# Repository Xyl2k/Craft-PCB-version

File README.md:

# CRAFT AVR Demo — Custom PCB and 3D Enclosure

This repository contains a custom **double-layer PCB** design and a **3D-printable enclosure** for running the [CRAFT demo](http://www.linusakesson.net/scene/craft/) by Linus Åkesson on an **ATmega88-20PU** microcontroller.

The project is developed in **Autodesk EAGLE** for the PCB layout and includes an **STL enclosure model** designed for FDM 3D printing.

---

## 📦 Contents

- `eagle/`: EAGLE schematic (`.sch`) and board layout (`.brd`)
- `enclosure/`: 3D enclosure model (`.stl`)
- `firmware/`: Precompiled HEX file and Flipper Zero-compatible firmware folder
- `README.md`: Project documentation

---

## ⚙️ Features

- Runs the original CRAFT demo at **20 MHz**
- Audio synthesized in real-time by the ATmega88
- Double-layer PCB with clear silkscreen labeling
- Compact size with mounting holes for enclosure
- Powered via ISP header or screw terminal in 3.3 volts

---

## 📋 Bill of Materials (BOM)

| Qty | Component              | Value/Type         |
|-----|------------------------|--------------------|
| x7  | Resistor               | 2 kΩ               |
| x6  | Resistor               | 1 kΩ               |
| x9  | Resistor               | 442 Ω              |
| x3  | Resistor               | 220 Ω              |
| x2  | Capacitor              | 22 pF              |
| x1  | Capacitor              | 10 µF              |
| x3  | Diode                  | 1N4148             |
| x1  | Transistor             | BC560C             |
| x1  | Trimmer Potentiometer  | 1 kΩ               |
| x1  | Microcontroller        | ATmega88-20PU      |
| x1  | Crystal Oscillator     | 20 MHz             |
| x1  | VGA Socket (Female)    | Through-hole       |
| x1  | RCA Socket (Female)    | Through-hole       |
| x1  | Screw Terminal         | 2-pin              |

---

## 🖨️ Enclosure

- Format: `.stl` for 3D printing
- Designed for FDM printers (0.4 mm nozzle recommended)
- Includes cutouts for VGA, RCA, power terminal, and ISP pins
- Snap-fit
- PCB enclosure case.STL need to be printed with support.

---

## 🛠️ Flashing the Firmware

The `firmware/` folder includes:

- `flash.hex` — Precompiled firmware for ATmega88-20PU
- `AVR Flasher/` — Folder structure compatible with **Flipper Zero**

### 🔧 Flashing with Flipper Zero

1. Copy the content of `AVR Flasher/` folder to your Flipper Zero's SD card in (`/apps_data/avr_isp/`).
2. Connect your Flipper to the CRAFT PCB via the ISP header.
3. Open the [**AVR Flasher**](https://lab.flipper.net/apps/avr_isp) app on your Flipper.
4. Select Craft_pcb.avr firmware and flash it directly to the ATmega88.

---

## 🧠 Credits

- **Original CRAFT demo** by [Linus Åkesson](http://www.linusakesson.net/)
- **PCB and enclosure design** by myself for my hackerspace.

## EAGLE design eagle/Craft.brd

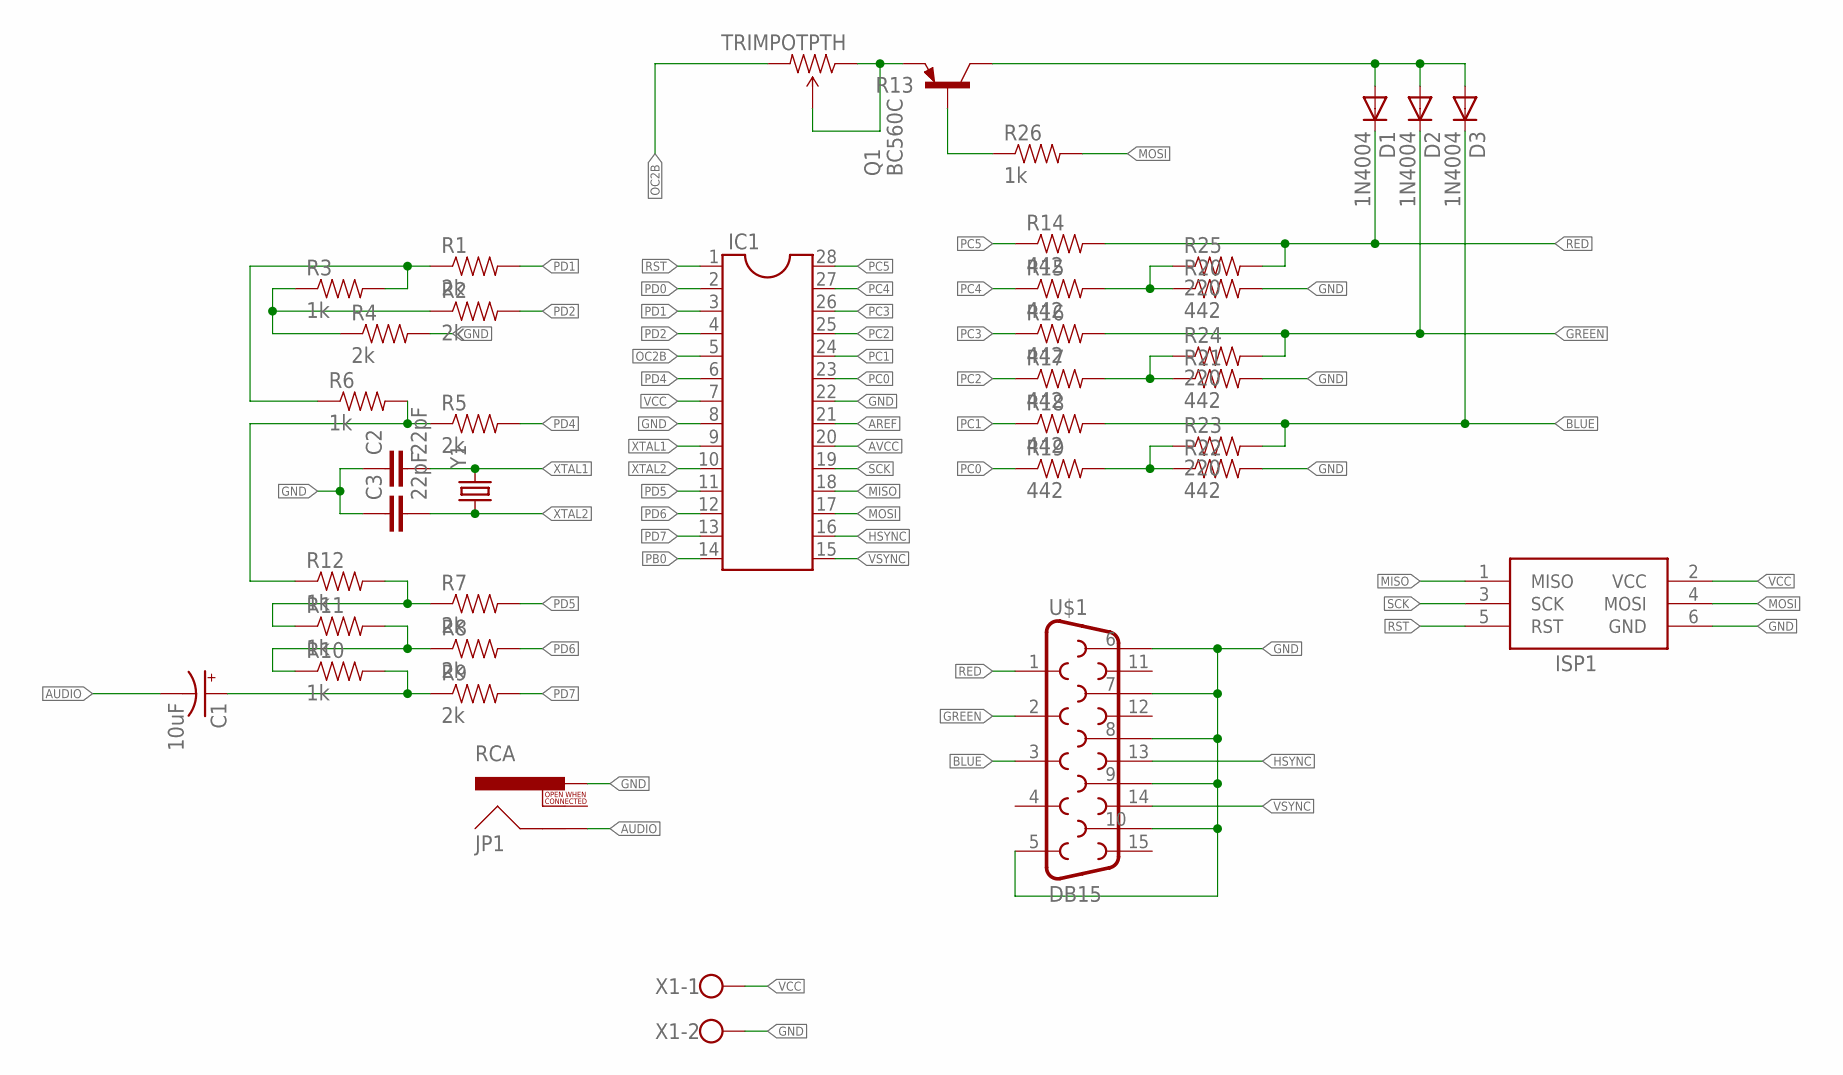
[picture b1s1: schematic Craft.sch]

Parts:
C1: 10uF; CPOL-RADIAL-100UF-25V
C2, C3: 22pF; CAP-PTH-SMALLEZ
D1, D2, D3: 1N4004; DO41-10
IC1: DIL28-3
ISP1: AVRISP-6; AVRISP
JP1: RCA
Q1: BC560C; TO92-EBC
R1, R2, R4, R5, R7, R8, R9: 2k; AXIAL-0.4
R3, R6, R10, R11, R12, R26: 1k; AXIAL-0.4
R13: TRIMPOTPTH; TRIM_POT_PTH
R14, R15, R16, R17, R18, R19, R20, R21, R22: 442; AXIAL-0.4
R23, R24, R25: 220; AXIAL-0.4
U$1: DB15
X1: W237-102
Y1: CRYSTALHC49UV; HC49U-V

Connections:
AREF: IC1.21
AUDIO: C1.2 (-), JP1.SHELL
AVCC: IC1.20
BLUE: D3.C, R18.P$2 (2), R23.P$2 (2), U$1.3
GND: C2.1, C3.1, IC1.8, IC1.22, ISP1.6 (GND), JP1.PIN, R4.P$2 (2), R20.P$2 (2), R21.P$2 (2), R22.P$2 (2), U$1.5, U$1.6, U$1.7, U$1.8, U$1.9, U$1.10, X1.2
GREEN: D2.C, R16.P$2 (2), R24.P$2 (2), U$1.2
HSYNC: IC1.16, U$1.13
MISO: IC1.18, ISP1.1 (MISO)
MOSI: IC1.17, ISP1.4 (MOSI), R26.P$2 (2)
unnamed: Q1.E, R13.1 (CCW), R13.2 (WIPER)
unnamed: D1.A, D2.A, D3.A, Q1.C
unnamed: Q1.B, R26.P$1 (1)
unnamed: R1.P$1 (1), R3.P$2 (2), R6.P$1 (1)
unnamed: R5.P$1 (1), R6.P$2 (2), R12.P$1 (1)
unnamed: R2.P$1 (1), R3.P$1 (1), R4.P$1 (1)
unnamed: C1.1 (+), R9.P$1 (1), R10.P$2 (2)
unnamed: R8.P$1 (1), R10.P$1 (1), R11.P$2 (2)
unnamed: R7.P$1 (1), R11.P$1 (1), R12.P$2 (2)
unnamed: R15.P$2 (2), R20.P$1 (1), R25.P$1 (1)
unnamed: R17.P$2 (2), R21.P$1 (1), R24.P$1 (1)
unnamed: R19.P$2 (2), R22.P$1 (1), R23.P$1 (1)
OC2B: IC1.5, R13.3 (CW)
PB0: IC1.14
PC0: IC1.23, R19.P$1 (1)
PC1: IC1.24, R18.P$1 (1)
PC2: IC1.25, R17.P$1 (1)
PC3: IC1.26, R16.P$1 (1)
PC4: IC1.27, R15.P$1 (1)
PC5: IC1.28, R14.P$1 (1)
PD0: IC1.2
PD1: IC1.3, R1.P$2 (2)
PD2: IC1.4, R2.P$2 (2)
PD4: IC1.6, R5.P$2 (2)
PD5: IC1.11, R7.P$2 (2)
PD6: IC1.12, R8.P$2 (2)
PD7: IC1.13, R9.P$2 (2)
RED: D1.C, R14.P$2 (2), R25.P$2 (2), U$1.1
RST: IC1.1, ISP1.5 (RST)
SCK: IC1.19, ISP1.3 (SCK)
VCC: IC1.7, ISP1.2 (VCC), X1.1
VSYNC: IC1.15, U$1.14
XTAL1: C2.2, IC1.9, Y1.2
XTAL2: C3.2, IC1.10, Y1.1

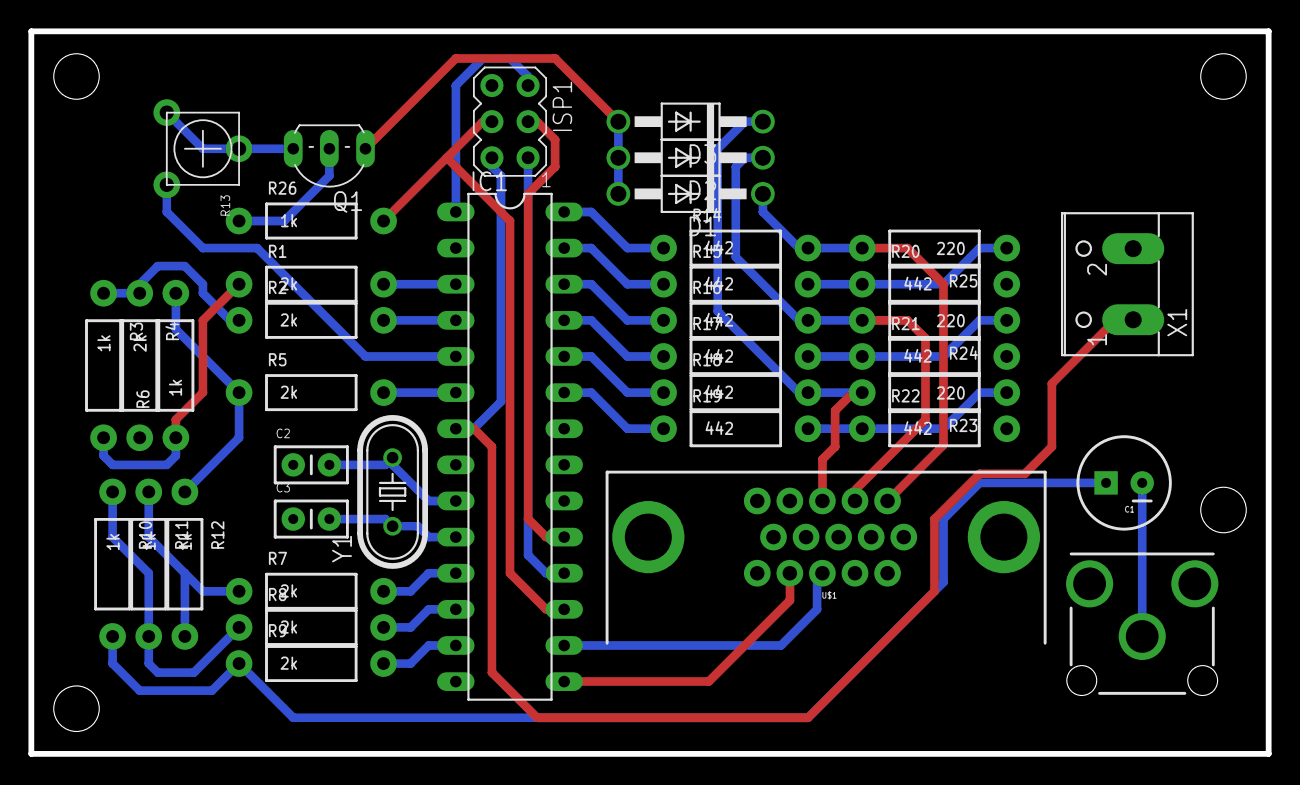
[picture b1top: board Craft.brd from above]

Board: 2 copper layers, 87.0 x 50.8 mm, 39 parts (0 on the bottom side), 39 nets.

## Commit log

2014-11-13 :lollipop: Added .gitattributes & .gitignore files
2014-11-13 v1.0
    v1.0 not tested
2014-11-13 v1.0
    v1.0
2014-12-17 pcb working
    just a small problem with the alimentation but i've you power it up from
    programation pin there is no problem, demmo is running.
    Don't forget to set the fuses correctly and select: Ext. Full-swing
    Crystal; Start-up time PWRDWN/RESET: 16K CK/14 CK + 65 ms
    for the raw eeprom image: avrdude -c usbtiny -p m88 -U
    eeprom:w:eeprom.raw
2014-12-19 part list
    part list
2014-12-19 firmware
    firmware
2025-05-08 Update round
    Update round

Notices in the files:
parts and their libraries:
SparkFun-Resistors: Licensing: Creative Commons ShareAlike 4.0 International - https://creativecommons.org/licenses/by-sa/4.0
